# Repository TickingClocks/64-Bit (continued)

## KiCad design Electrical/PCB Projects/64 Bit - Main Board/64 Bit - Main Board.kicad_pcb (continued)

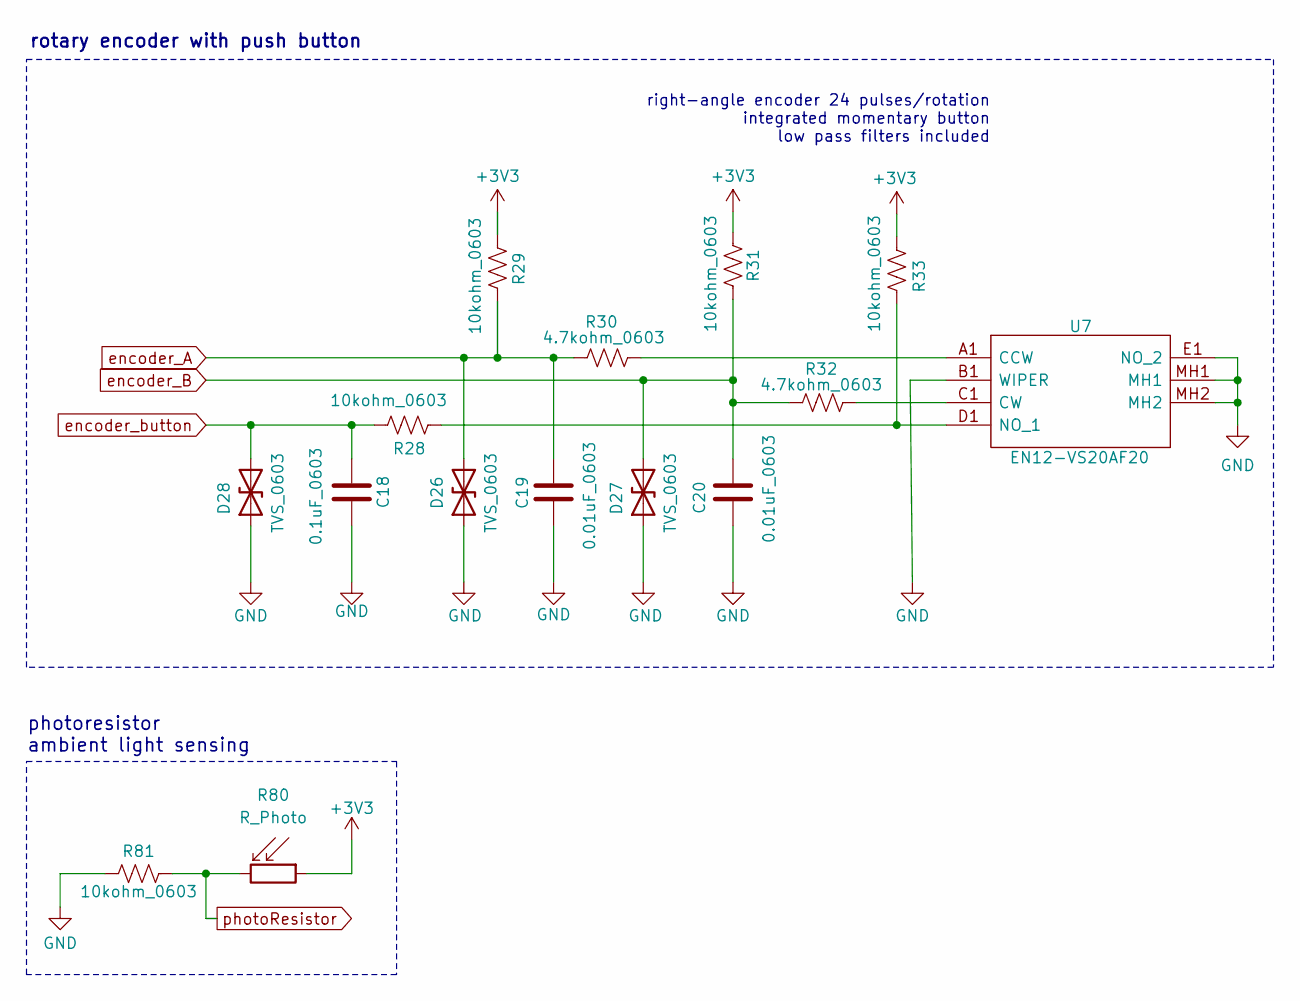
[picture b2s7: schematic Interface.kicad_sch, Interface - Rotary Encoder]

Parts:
C18: 0.1uF_0603; C_0603_1608Metric
C19, C20: 0.01uF_0603; C_0603_1608Metric
D26, D27, D28: TVS_0603; R_0603_1608Metric
R28, R29, R31, R33, R81: 10kohm_0603; R_0603_1608Metric
R30, R32: 4.7kohm_0603; R_0603_1608Metric
R80: R_Photo; R_LDR_5.1x4.3mm_P3.4mm_Vertical
U7: EN12-VS20AF20; Mouser Part Number 858-EN12VS20AF20

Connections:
+3V3: R29.1, R31.1, R33.2, R80.1; also elsewhere on the board
GND: C18.2, C19.1, C20.2, D26.1 (A1), D27.1 (A1), D28.1 (A1), R81.1, U7.B1 (WIPER), U7.E1 (NO_2), U7.MH1, U7.MH2; also elsewhere on the board
unnamed: R30.2, U7.A1 (CCW)
unnamed: R32.2, U7.C1 (CW)
unnamed: R28.1, R33.1, U7.D1 (NO_1)
encoder_A: C19.2, D26.2 (A2), R29.2, R30.1; also elsewhere on the board
encoder_B: C20.1, D27.2 (A2), R31.2, R32.1; also elsewhere on the board
encoder_button: C18.1, D28.2 (A2), R28.2; also elsewhere on the board
photoResistor: R80.2, R81.2; also elsewhere on the board

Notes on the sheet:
right-angle encoder 24 pulses/rotation integrated momentary button low pass filters included
photoresistor ambient light sensing
rotary encoder with push button

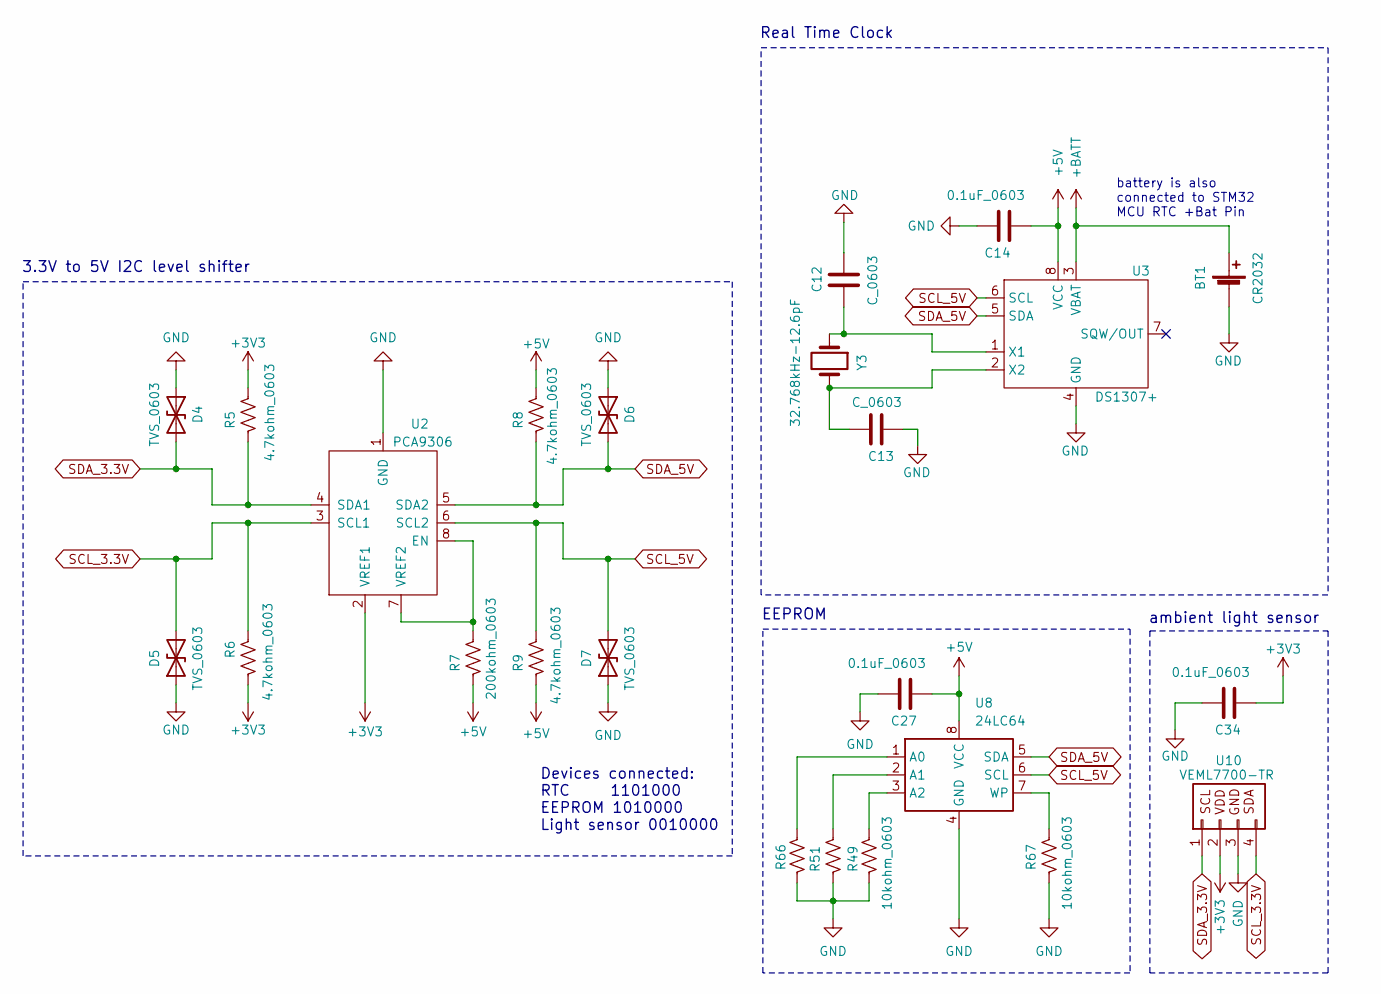
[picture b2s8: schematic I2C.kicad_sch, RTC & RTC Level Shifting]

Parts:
BT1: CR2032; CR2030_HLDR
C12, C13: C_0603; C_0603_1608Metric
C14, C27, C34: 0.1uF_0603; C_0603_1608Metric
D4, D5, D6, D7: TVS_0603; R_0603_1608Metric
R5, R6, R8, R9: 4.7kohm_0603; R_0603_1608Metric
R7: 200kohm_0603; R_0603_1608Metric
R49, R51, R66, R67: 10kohm_0603; R_0603_1608Metric
U2: PCA9306
U3: DS1307+; DS1307
U8: 24LC64; 24LC64F-ISN
U10: VEML7700-TR; VEML7700
Y3: 32.768kHz-12.6pF; 37.768kHz

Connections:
+3V3: C34.2, R5.2, R6.1, U2.2 (VREF1), U10.2 (VDD); also elsewhere on the board
+5V: C14.2, C27.2, R7.1, R8.2, R9.1, U3.8 (VCC), U8.8 (VCC); also elsewhere on the board
+BATT: BT1.1 (+), U3.3 (VBAT); also elsewhere on the board
GND: BT1.2 (-), C12.2, C13.1, C14.1, C27.1, C34.1, D4.1 (A1), D5.1 (A1), D6.1 (A1), D7.1 (A1), R49.1, R51.1, R66.1, R67.1, U2.1 (GND), U3.4 (GND), U8.4 (GND), U10.3 (GND); also elsewhere on the board
unnamed: R7.2, U2.7 (VREF2), U2.8 (EN)
unnamed: C12.1, U3.1 (X1), Y3.1
unnamed: C13.2, U3.2 (X2), Y3.2
unnamed: R66.2, U8.1 (A0)
unnamed: R51.2, U8.2 (A1)
unnamed: R49.2, U8.3 (A2)
unnamed: R67.2, U8.7 (WP)
SCL_3.3V: D5.2 (A2), R6.2, U2.3 (SCL1), U10.4 (SDA); also elsewhere on the board
SCL_5V: D7.2 (A2), R9.2, U2.6 (SCL2), U3.6 (SCL), U8.6 (SCL); also elsewhere on the board
SDA_3.3V: D4.2 (A2), R5.1, U2.4 (SDA1), U10.1 (SCL); also elsewhere on the board
SDA_5V: D6.2 (A2), R8.1, U2.5 (SDA2), U3.5 (SDA), U8.5 (SDA); also elsewhere on the board

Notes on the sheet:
battery is also connected to STM32 MCU RTC +Bat Pin
Devices connected: RTC 1101000 EEPROM 1010000 Light sensor 0010000
Real Time Clock
ambient light sensor
EEPROM
3.3V to 5V I2C level shifter

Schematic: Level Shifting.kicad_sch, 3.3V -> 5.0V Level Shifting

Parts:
C15, C16, C17: 0.1uF_0603; C_0603_1608Metric
D8, D9, D10, D11, D12, D13, D14, D15, D16, D17, D18, D19, D20, D21, D22, D23, D24, D25: TVS_0603; R_0603_1608Metric
R10, R11, R12, R13, R14, R15, R16, R17, R18, R19, R21, R25, R26, R27: 300ohm_0603; R_0603_1608Metric
R20, R22, R23, R24: 22ohm_0603; R_0603_1608Metric
U4, U5, U6: 74HC3G34DC

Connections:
+5V: C15.1, C16.1, C17.1, U4.8 (VCC), U5.8 (VCC), U6.8 (VCC); also elsewhere on the board
GND: C15.2, C16.2, C17.2, D8.1 (A1), D9.1 (A1), D10.1 (A1), D11.1 (A1), D12.1 (A1), D13.1 (A1), D14.1 (A1), D15.1 (A1), D16.1 (A1), D17.1 (A1), D18.1 (A1), D19.1 (A1), D20.1 (A1), D21.1 (A1), D22.1 (A1), D23.1 (A1), D24.1 (A1), D25.1 (A1), U4.4 (GND), U5.4 (GND), U6.4 (GND); also elsewhere on the board
MCU_safetyEnable_1: R15.2; also elsewhere on the board
MCU_safetyEnable_1_5V: R24.1; also elsewhere on the board
MCU_safetyEnable_2: R13.2; also elsewhere on the board
MCU_safetyEnable_2_5V: R22.1; also elsewhere on the board
unnamed: D8.2 (A2), R16.1, U4.1 (1A)
unnamed: D9.2 (A2), R10.1, U5.1 (1A)
unnamed: D10.2 (A2), R13.1, U6.1 (1A)
unnamed: D11.2 (A2), R17.1, U4.3 (2A)
unnamed: D12.2 (A2), R11.1, U5.3 (2A)
unnamed: D13.2 (A2), R14.1, U6.3 (2A)
unnamed: D14.2 (A2), R18.1, U4.6 (3A)
unnamed: D15.2 (A2), R12.2, U5.6 (3A)
unnamed: D16.2 (A2), R15.1, U6.6 (3A)
unnamed: D17.2 (A2), R24.2, U6.2 (3Y)
unnamed: D18.2 (A2), R27.1, U4.2 (3Y)
unnamed: D19.2 (A2), R21.1, U5.2 (3Y)
unnamed: D20.2 (A2), R23.2, U6.5 (2Y)
unnamed: D21.2 (A2), R26.2, U4.5 (2Y)
unnamed: D22.2 (A2), R20.2, U5.5 (2Y)
unnamed: D23.2 (A2), R22.2, U6.7 (1Y)
unnamed: D24.2 (A2), R25.2, U4.7 (1Y)
unnamed: D25.2 (A2), R19.2, U5.7 (1Y)
hv_output_relay: R23.1; also elsewhere on the board
mcu_hv_output_relay: R14.2; also elsewhere on the board
mcu_neopixel: R11.2; also elsewhere on the board
mcu_nixie_RCLK: R12.1; also elsewhere on the board
mcu_nixie_SRCK: R16.2; also elsewhere on the board
mcu_nixie_SRCLK: R17.2; also elsewhere on the board
mcu_nixie_data: R18.2; also elsewhere on the board
mcu_nixie_display_enable: R10.2; also elsewhere on the board
neopixel: R20.1; also elsewhere on the board
nixie_RCLK: R21.2; also elsewhere on the board
nixie_SRCK: R25.1; also elsewhere on the board
nixie_SRCLK: R26.1; also elsewhere on the board
nixie_data: R27.2; also elsewhere on the board
nixie_display_enable: R19.1; also elsewhere on the board

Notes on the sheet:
safetyEnable Signals from MCU
shift register signals from MCU
shift register signals to display PCB
neopixel to display PCB
neopixel from MCU
safetyEnable Signals to transistors

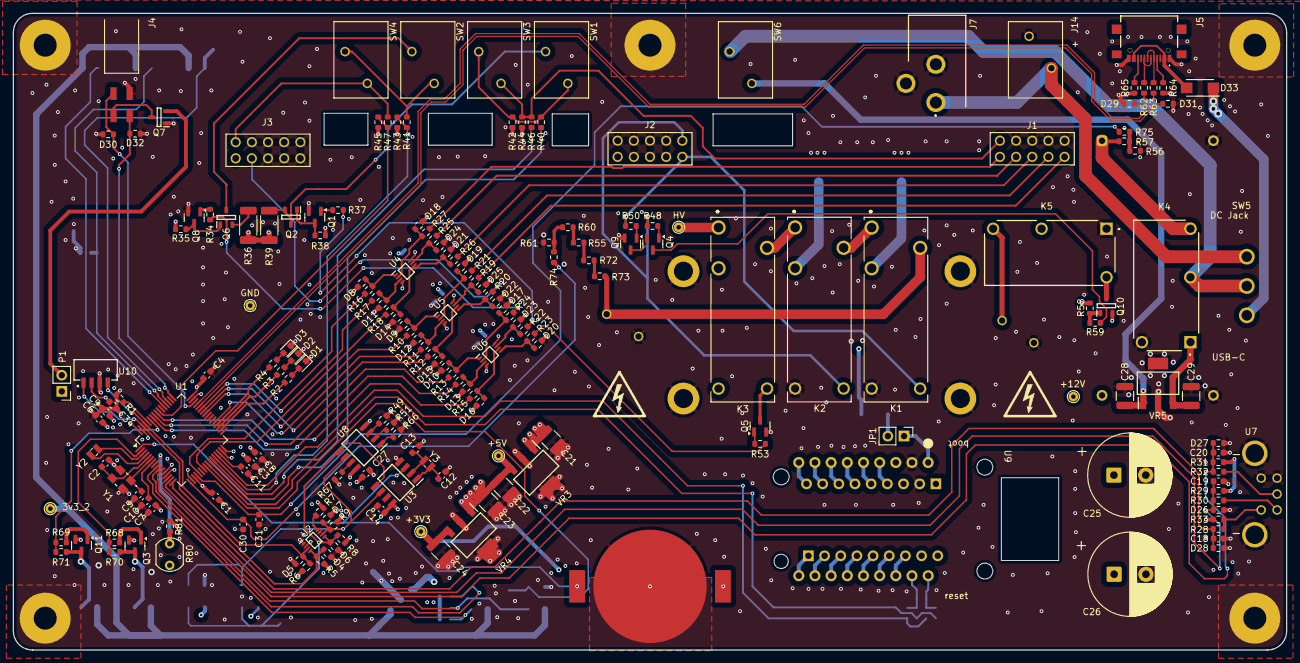
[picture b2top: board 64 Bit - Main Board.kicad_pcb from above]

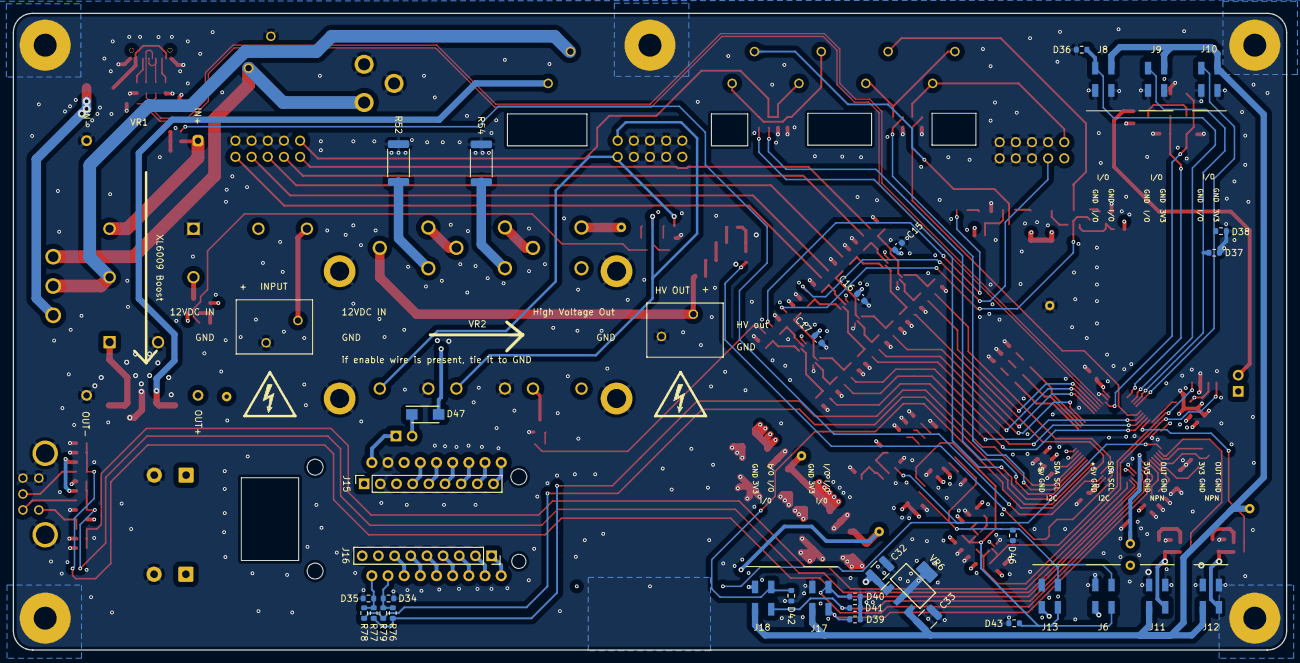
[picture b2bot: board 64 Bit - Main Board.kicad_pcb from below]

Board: 4 copper layers, 200.0 x 100.0 mm, 233 parts (37 on the bottom side), 162 nets.

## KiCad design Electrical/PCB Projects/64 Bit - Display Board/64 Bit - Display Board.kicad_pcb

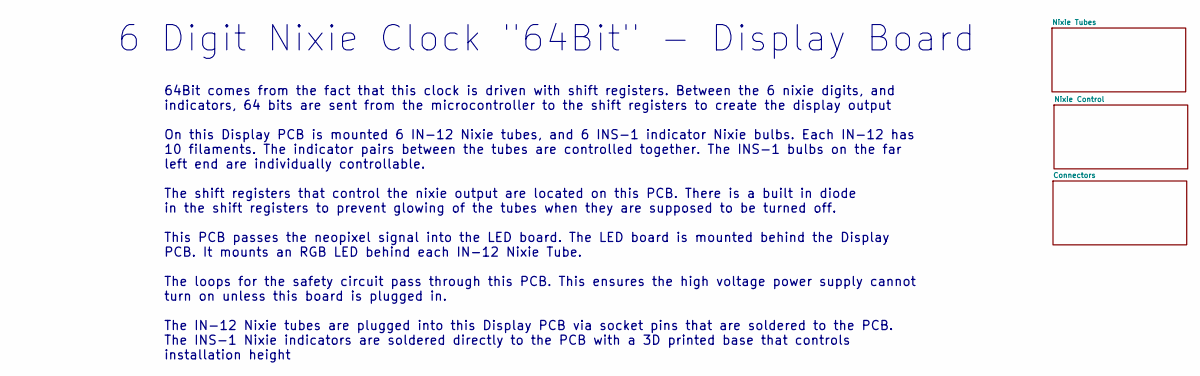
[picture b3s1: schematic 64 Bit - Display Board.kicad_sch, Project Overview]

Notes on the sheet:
6 Digit Nixie Clock "64Bit" - Display Board
64Bit comes from the fact that this clock is driven with shift registers. Between the 6 nixie digits, and indicators, 64 bits are sent from the microcontroller to the shift registers to create the display output On this Display PCB is mounted 6 IN-12 Nixie tubes, and 6 INS-1 indicator Nixie bulbs. 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

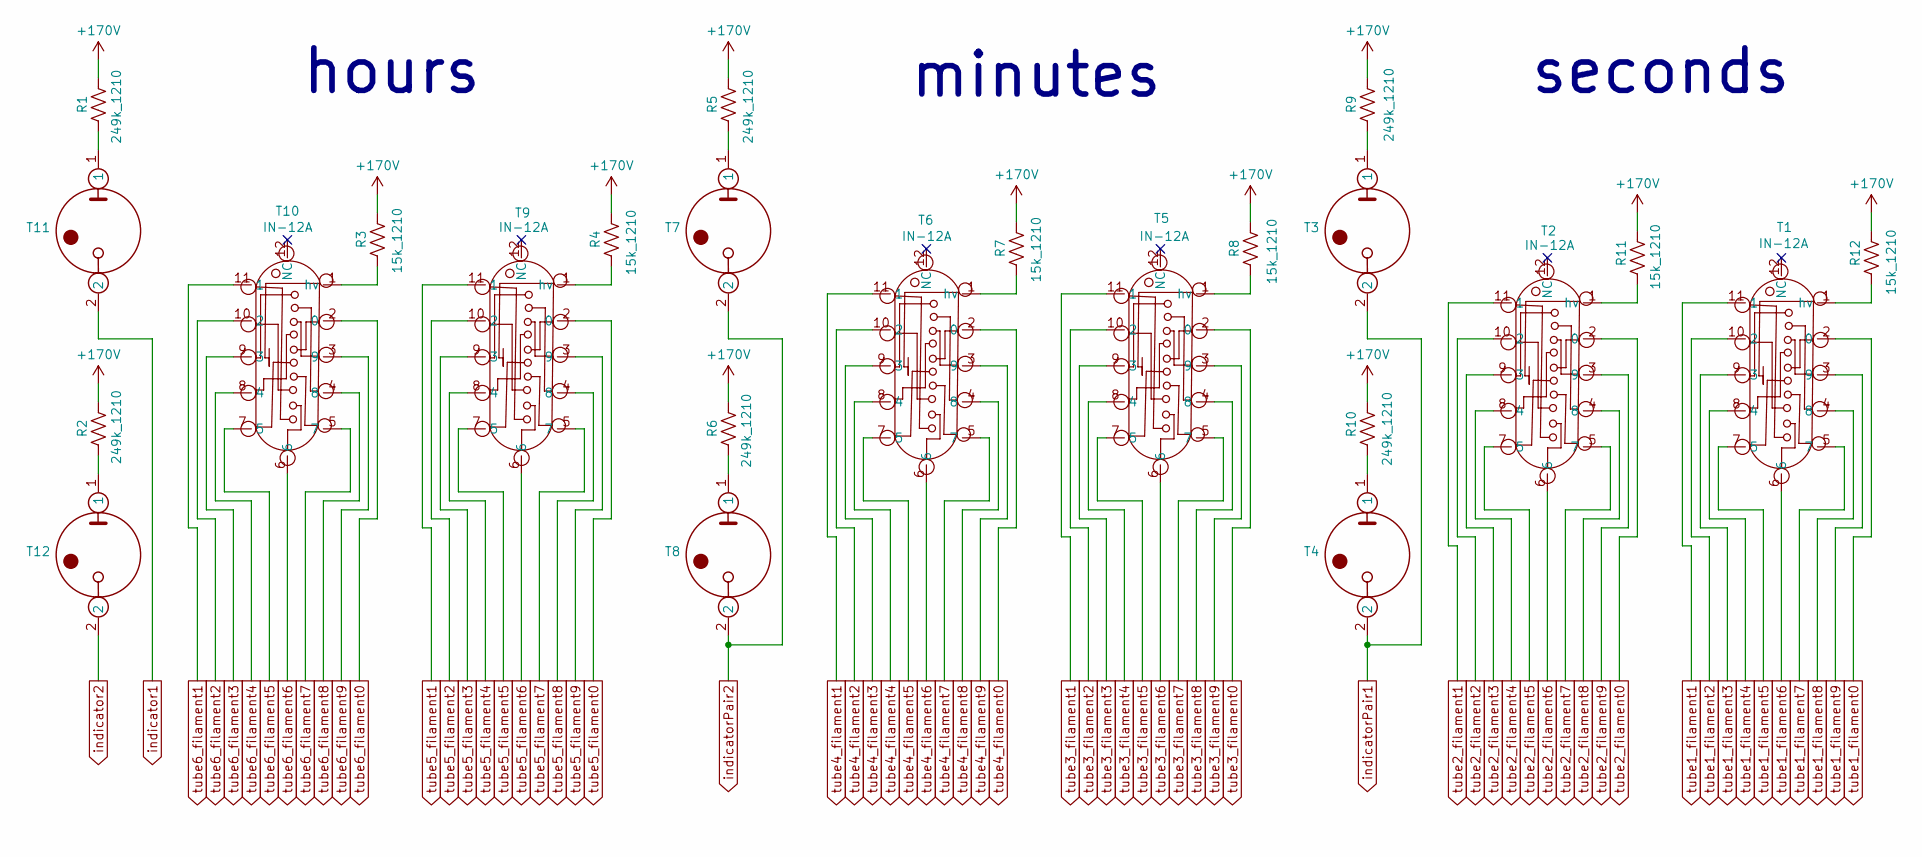
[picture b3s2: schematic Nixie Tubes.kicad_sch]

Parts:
R1, R2, R5, R6, R9, R10: 249k_1210; C_1210_3225Metric
R3, R4, R7, R8, R11, R12: 15k_1210; C_1210_3225Metric
T1, T2, T5, T6, T9, T10: IN-12A; IN-12
T3, T4, T7, T8, T11, T12: INS-1

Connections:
+170V: R1.1, R2.1, R3.1, R4.1, R5.1, R6.1, R7.1, R8.1, R9.1, R10.1, R11.1, R12.1; also elsewhere on the board
unnamed: R1.2, T11.1
unnamed: R2.2, T12.1
unnamed: R5.2, T7.1
unnamed: R6.2, T8.1
unnamed: R9.2, T3.1
unnamed: R10.2, T4.1
unnamed: R12.2, T1.1 (hv)
unnamed: R11.2, T2.1 (hv)
unnamed: R8.2, T5.1 (hv)
unnamed: R7.2, T6.1 (hv)
unnamed: R4.2, T9.1 (hv)
unnamed: R3.2, T10.1 (hv)
indicator1: T11.2; also elsewhere on the board
indicator2: T12.2; also elsewhere on the board
indicatorPair1: T3.2, T4.2; also elsewhere on the board
indicatorPair2: T7.2, T8.2; also elsewhere on the board
tube1_filament0: T1.2 (0); also elsewhere on the board
tube1_filament1: T1.11 (1); also elsewhere on the board
tube1_filament2: T1.10 (2); also elsewhere on the board
tube1_filament3: T1.9 (3); also elsewhere on the board
tube1_filament4: T1.8 (4); also elsewhere on the board
tube1_filament5: T1.7 (5); also elsewhere on the board
tube1_filament6: T1.6; also elsewhere on the board
tube1_filament7: T1.5 (7); also elsewhere on the board
tube1_filament8: T1.4 (8); also elsewhere on the board
tube1_filament9: T1.3 (9); also elsewhere on the board
tube2_filament0: T2.2 (0); also elsewhere on the board
tube2_filament1: T2.11 (1); also elsewhere on the board
tube2_filament2: T2.10 (2); also elsewhere on the board
tube2_filament3: T2.9 (3); also elsewhere on the board
tube2_filament4: T2.8 (4); also elsewhere on the board
tube2_filament5: T2.7 (5); also elsewhere on the board
tube2_filament6: T2.6; also elsewhere on the board
tube2_filament7: T2.5 (7); also elsewhere on the board
tube2_filament8: T2.4 (8); also elsewhere on the board
tube2_filament9: T2.3 (9); also elsewhere on the board
tube3_filament0: T5.2 (0); also elsewhere on the board
tube3_filament1: T5.11 (1); also elsewhere on the board
tube3_filament2: T5.10 (2); also elsewhere on the board
tube3_filament3: T5.9 (3); also elsewhere on the board
tube3_filament4: T5.8 (4); also elsewhere on the board
tube3_filament5: T5.7 (5); also elsewhere on the board
tube3_filament6: T5.6; also elsewhere on the board
tube3_filament7: T5.5 (7); also elsewhere on the board
tube3_filament8: T5.4 (8); also elsewhere on the board
tube3_filament9: T5.3 (9); also elsewhere on the board
tube4_filament0: T6.2 (0); also elsewhere on the board
tube4_filament1: T6.11 (1); also elsewhere on the board
tube4_filament2: T6.10 (2); also elsewhere on the board
tube4_filament3: T6.9 (3); also elsewhere on the board
tube4_filament4: T6.8 (4); also elsewhere on the board
tube4_filament5: T6.7 (5); also elsewhere on the board
tube4_filament6: T6.6; also elsewhere on the board
tube4_filament7: T6.5 (7); also elsewhere on the board
tube4_filament8: T6.4 (8); also elsewhere on the board
tube4_filament9: T6.3 (9); also elsewhere on the board
tube5_filament0: T9.2 (0); also elsewhere on the board
tube5_filament1: T9.11 (1); also elsewhere on the board
tube5_filament2: T9.10 (2); also elsewhere on the board
tube5_filament3: T9.9 (3); also elsewhere on the board
tube5_filament4: T9.8 (4); also elsewhere on the board
tube5_filament5: T9.7 (5); also elsewhere on the board
tube5_filament6: T9.6; also elsewhere on the board
tube5_filament7: T9.5 (7); also elsewhere on the board
tube5_filament8: T9.4 (8); also elsewhere on the board
tube5_filament9: T9.3 (9); also elsewhere on the board
tube6_filament0: T10.2 (0); also elsewhere on the board
tube6_filament1: T10.11 (1); also elsewhere on the board
tube6_filament2: T10.10 (2); also elsewhere on the board
tube6_filament3: T10.9 (3); also elsewhere on the board
tube6_filament4: T10.8 (4); also elsewhere on the board
tube6_filament5: T10.7 (5); also elsewhere on the board
tube6_filament6: T10.6; also elsewhere on the board
tube6_filament7: T10.5 (7); also elsewhere on the board
tube6_filament8: T10.4 (8); also elsewhere on the board
tube6_filament9: T10.3 (9); also elsewhere on the board

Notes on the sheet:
minutes
seconds
hours

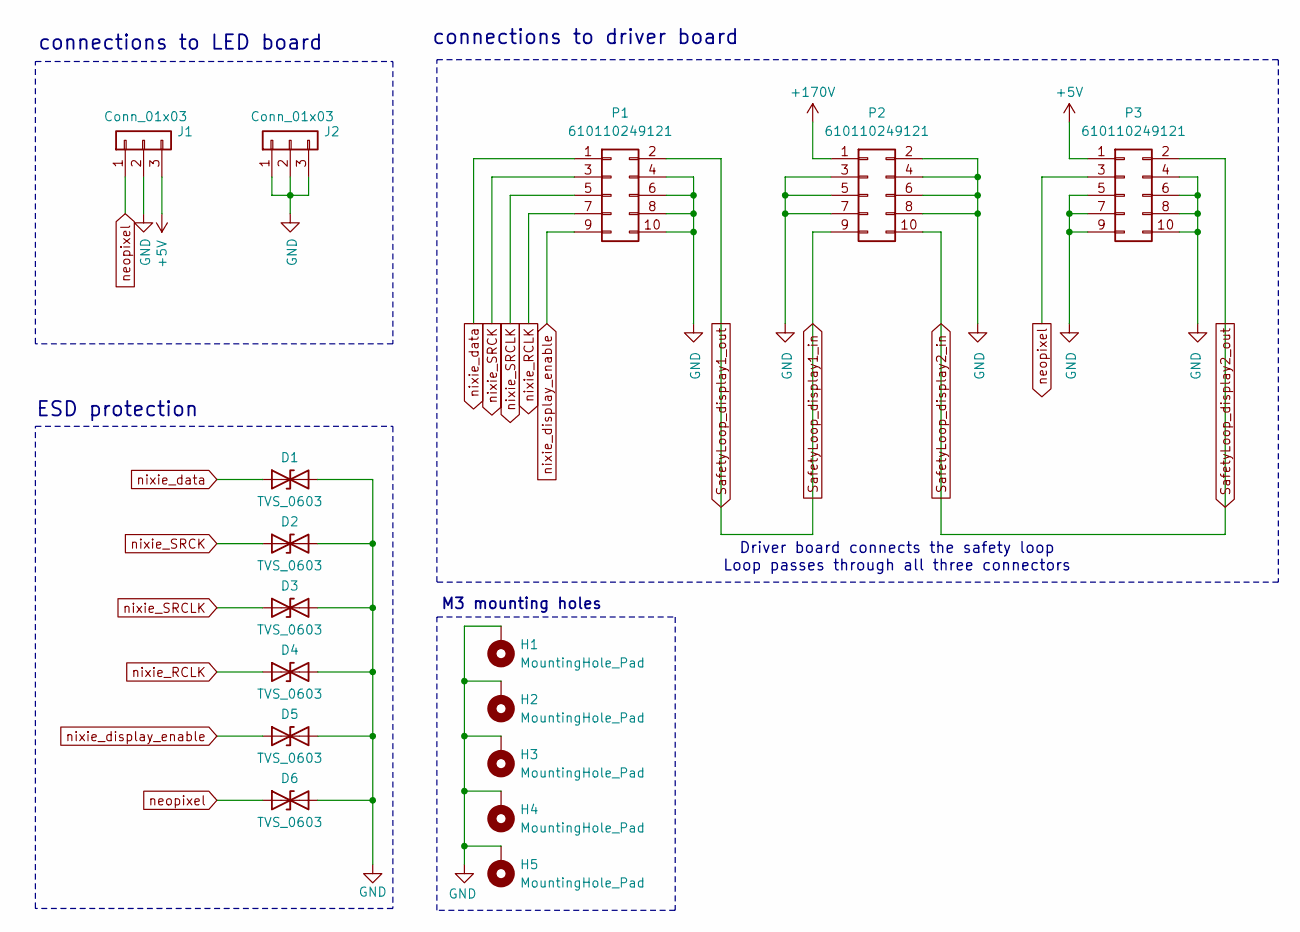
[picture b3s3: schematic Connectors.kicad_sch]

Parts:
D1, D2, D3, D4, D5, D6: TVS_0603; R_0603_1608Metric
H1, H2, H3, H4, H5: MountingHole_Pad; M3 Standoff Footprint
J1, J2: Conn_01x03; PinSocket_1x03_P2.54mm_Vertical
P1, P2, P3: 610110249121

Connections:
+5V: J1.3, P3.1; also elsewhere on the board
+170V: P2.1; also elsewhere on the board
GND: D1.2 (A2), D2.2 (A2), D3.2 (A2), D4.2 (A2), D5.2 (A2), D6.2 (A2), H1.1, H2.1, H3.1, H4.1, H5.1, J1.2, J2.1, J2.2, J2.3, P1.4, P1.6, P1.8, P1.10, P2.2, P2.3, P2.4, P2.5, P2.6, P2.7, P2.8, P3.4, P3.5, P3.6, P3.7, P3.8, P3.9, P3.10; also elsewhere on the board
SafetyLoop_display1_in: P1.2, P2.9
SafetyLoop_display2_in: P2.10, P3.2
neopixel: D6.1 (A1), J1.1, P3.3
nixie_RCLK: D4.1 (A1), P1.7; also elsewhere on the board
nixie_SRCK: D2.1 (A1), P1.3; also elsewhere on the board
nixie_SRCLK: D3.1 (A1), P1.5; also elsewhere on the board
nixie_data: D1.1 (A1), P1.1; also elsewhere on the board
nixie_display_enable: D5.1 (A1), P1.9; also elsewhere on the board

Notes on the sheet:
Driver board connects the safety loop Loop passes through all three connectors
connections to driver board
connections to LED board
ESD protection
M3 mounting holes

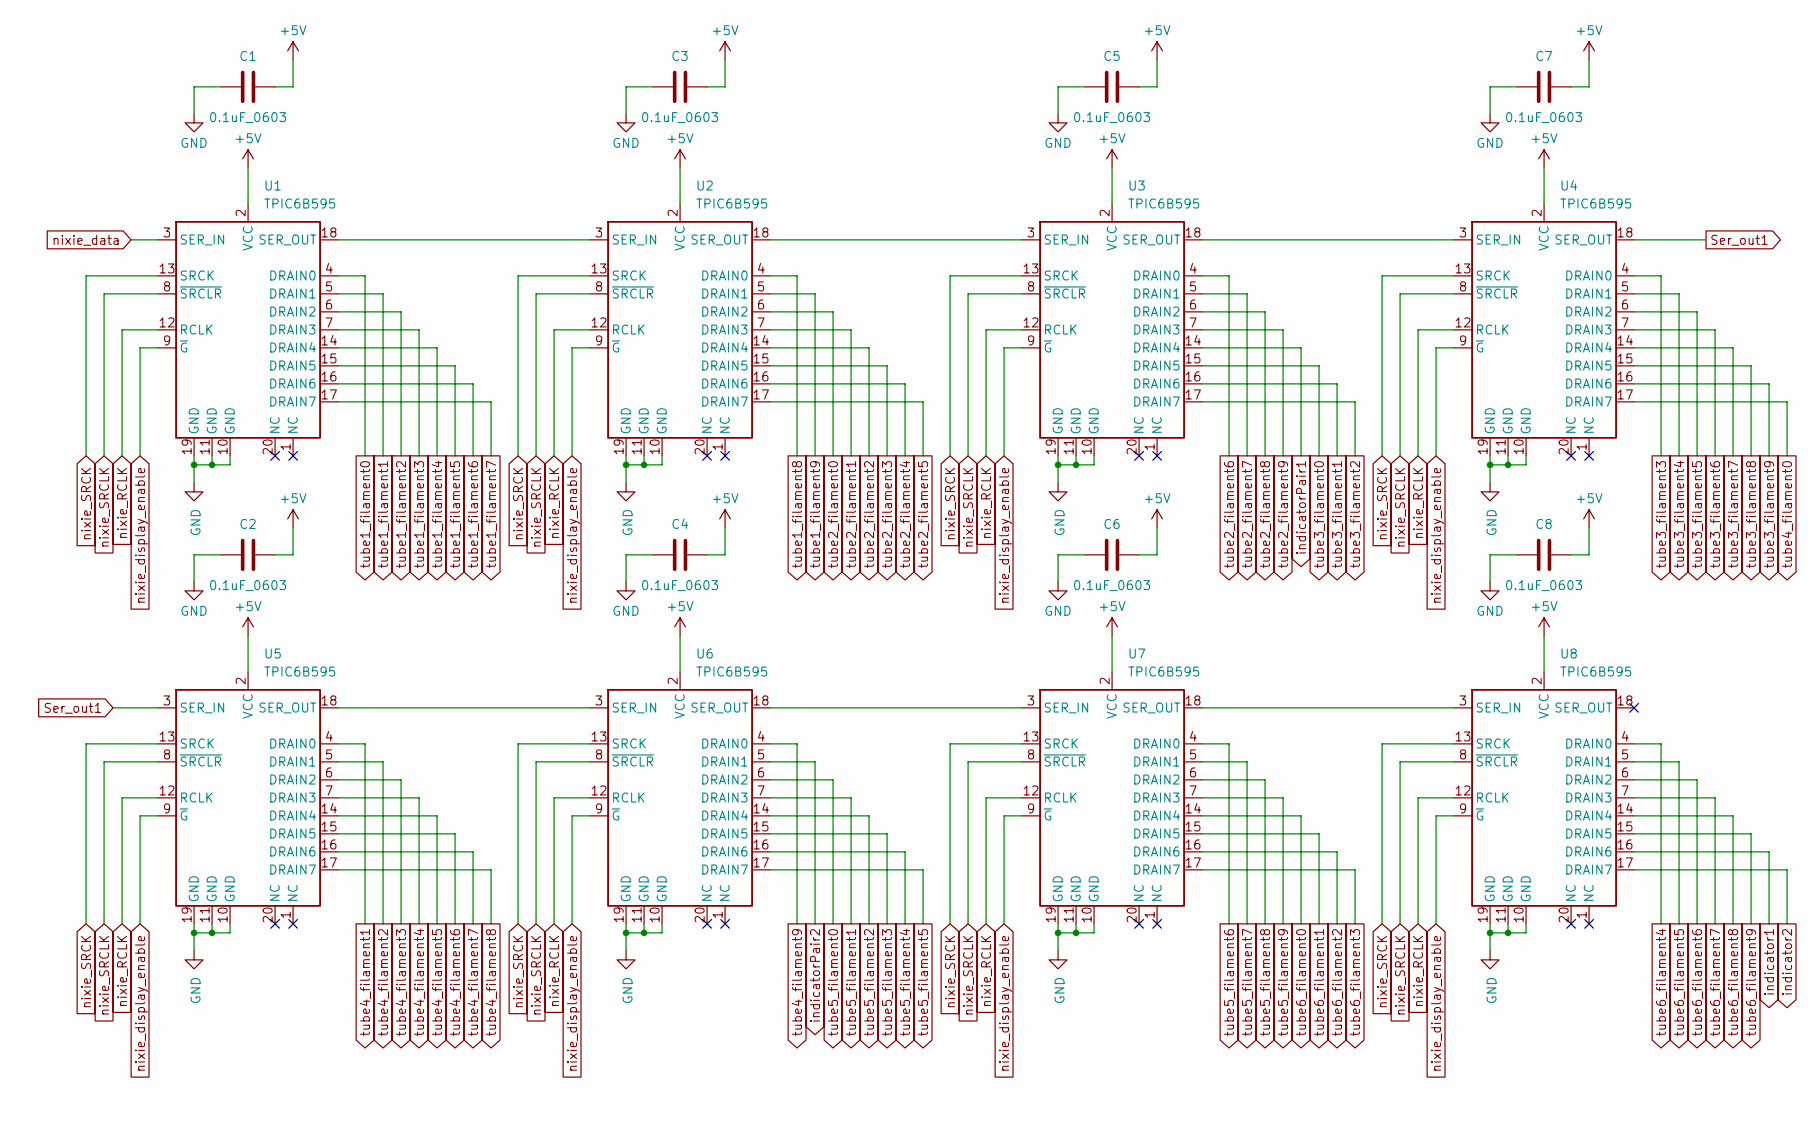
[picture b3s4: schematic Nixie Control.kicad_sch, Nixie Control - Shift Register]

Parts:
C1, C2, C3, C4, C5, C6, C7, C8: 0.1uF_0603; C_0603_1608Metric
U1, U2, U3, U4, U5, U6, U7, U8: TPIC6B595; TPIC6B595DWR

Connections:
+5V: C1.2, C2.2, C3.2, C4.2, C5.2, C6.2, C7.2, C8.2, U1.2 (VCC), U2.2 (VCC), U3.2 (VCC), U4.2 (VCC), U5.2 (VCC), U6.2 (VCC), U7.2 (VCC), U8.2 (VCC); also elsewhere on the board
GND: C1.1, C2.1, C3.1, C4.1, C5.1, C6.1, C7.1, C8.1, U1.10 (GND), U1.11 (GND), U1.19 (GND), U2.10 (GND), U2.11 (GND), U2.19 (GND), U3.10 (GND), U3.11 (GND), U3.19 (GND), U4.10 (GND), U4.11 (GND), U4.19 (GND), U5.10 (GND), U5.11 (GND), U5.19 (GND), U6.10 (GND), U6.11 (GND), U6.19 (GND), U7.10 (GND), U7.11 (GND), U7.19 (GND), U8.10 (GND), U8.11 (GND), U8.19 (GND); also elsewhere on the board
unnamed: U1.18 (SER_OUT), U2.3 (SER_IN)
unnamed: U2.18 (SER_OUT), U3.3 (SER_IN)
unnamed: U3.18 (SER_OUT), U4.3 (SER_IN)
unnamed: U5.18 (SER_OUT), U6.3 (SER_IN)
unnamed: U6.18 (SER_OUT), U7.3 (SER_IN)
unnamed: U7.18 (SER_OUT), U8.3 (SER_IN)
Ser_out1: U4.18 (SER_OUT), U5.3 (SER_IN)
indicator1: U8.16 (DRAIN6); also elsewhere on the board
indicator2: U8.17 (DRAIN7); also elsewhere on the board
indicatorPair1: U3.14 (DRAIN4); also elsewhere on the board
indicatorPair2: U6.5 (DRAIN1); also elsewhere on the board
nixie_RCLK: U1.12 (RCLK), U2.12 (RCLK), U3.12 (RCLK), U4.12 (RCLK), U5.12 (RCLK), U6.12 (RCLK), U7.12 (RCLK), U8.12 (RCLK); also elsewhere on the board
nixie_SRCK: U1.13 (SRCK), U2.13 (SRCK), U3.13 (SRCK), U4.13 (SRCK), U5.13 (SRCK), U6.13 (SRCK), U7.13 (SRCK), U8.13 (SRCK); also elsewhere on the board
nixie_SRCLK: U1.8 (~SRCLR), U2.8 (~SRCLR), U3.8 (~SRCLR), U4.8 (~SRCLR), U5.8 (~SRCLR), U6.8 (~SRCLR), U7.8 (~SRCLR), U8.8 (~SRCLR); also elsewhere on the board
nixie_data: U1.3 (SER_IN); also elsewhere on the board
nixie_display_enable: U1.9 (~G), U2.9 (~G), U3.9 (~G), U4.9 (~G), U5.9 (~G), U6.9 (~G), U7.9 (~G), U8.9 (~G); also elsewhere on the board
tube1_filament0: U1.4 (DRAIN0); also elsewhere on the board
tube1_filament1: U1.5 (DRAIN1); also elsewhere on the board
tube1_filament2: U1.6 (DRAIN2); also elsewhere on the board
tube1_filament3: U1.7 (DRAIN3); also elsewhere on the board
tube1_filament4: U1.14 (DRAIN4); also elsewhere on the board
tube1_filament5: U1.15 (DRAIN5); also elsewhere on the board
tube1_filament6: U1.16 (DRAIN6); also elsewhere on the board
tube1_filament7: U1.17 (DRAIN7); also elsewhere on the board
tube1_filament8: U2.4 (DRAIN0); also elsewhere on the board
tube1_filament9: U2.5 (DRAIN1); also elsewhere on the board
tube2_filament0: U2.6 (DRAIN2); also elsewhere on the board
tube2_filament1: U2.7 (DRAIN3); also elsewhere on the board
tube2_filament2: U2.14 (DRAIN4); also elsewhere on the board
tube2_filament3: U2.15 (DRAIN5); also elsewhere on the board
tube2_filament4: U2.16 (DRAIN6); also elsewhere on the board
tube2_filament5: U2.17 (DRAIN7); also elsewhere on the board
tube2_filament6: U3.4 (DRAIN0); also elsewhere on the board
tube2_filament7: U3.5 (DRAIN1); also elsewhere on the board
tube2_filament8: U3.6 (DRAIN2); also elsewhere on the board
tube2_filament9: U3.7 (DRAIN3); also elsewhere on the board
tube3_filament0: U3.15 (DRAIN5); also elsewhere on the board
tube3_filament1: U3.16 (DRAIN6); also elsewhere on the board
tube3_filament2: U3.17 (DRAIN7); also elsewhere on the board
tube3_filament3: U4.4 (DRAIN0); also elsewhere on the board
tube3_filament4: U4.5 (DRAIN1); also elsewhere on the board
tube3_filament5: U4.6 (DRAIN2); also elsewhere on the board
tube3_filament6: U4.7 (DRAIN3); also elsewhere on the board
tube3_filament7: U4.14 (DRAIN4); also elsewhere on the board
tube3_filament8: U4.15 (DRAIN5); also elsewhere on the board
tube3_filament9: U4.16 (DRAIN6); also elsewhere on the board
tube4_filament0: U4.17 (DRAIN7); also elsewhere on the board
tube4_filament1: U5.4 (DRAIN0); also elsewhere on the board
tube4_filament2: U5.5 (DRAIN1); also elsewhere on the board
tube4_filament3: U5.6 (DRAIN2); also elsewhere on the board
tube4_filament4: U5.7 (DRAIN3); also elsewhere on the board
tube4_filament5: U5.14 (DRAIN4); also elsewhere on the board
tube4_filament6: U5.15 (DRAIN5); also elsewhere on the board
tube4_filament7: U5.16 (DRAIN6); also elsewhere on the board
tube4_filament8: U5.17 (DRAIN7); also elsewhere on the board
tube4_filament9: U6.4 (DRAIN0); also elsewhere on the board
tube5_filament0: U6.6 (DRAIN2); also elsewhere on the board
tube5_filament1: U6.7 (DRAIN3); also elsewhere on the board
tube5_filament2: U6.14 (DRAIN4); also elsewhere on the board
tube5_filament3: U6.15 (DRAIN5); also elsewhere on the board
tube5_filament4: U6.16 (DRAIN6); also elsewhere on the board
tube5_filament5: U6.17 (DRAIN7); also elsewhere on the board
tube5_filament6: U7.4 (DRAIN0); also elsewhere on the board
tube5_filament7: U7.5 (DRAIN1); also elsewhere on the board
tube5_filament8: U7.6 (DRAIN2); also elsewhere on the board
tube5_filament9: U7.7 (DRAIN3); also elsewhere on the board
tube6_filament0: U7.14 (DRAIN4); also elsewhere on the board
tube6_filament1: U7.15 (DRAIN5); also elsewhere on the board
tube6_filament2: U7.16 (DRAIN6); also elsewhere on the board
tube6_filament3: U7.17 (DRAIN7); also elsewhere on the board
tube6_filament4: U8.4 (DRAIN0); also elsewhere on the board
tube6_filament5: U8.5 (DRAIN1); also elsewhere on the board
tube6_filament6: U8.6 (DRAIN2); also elsewhere on the board
tube6_filament7: U8.7 (DRAIN3); also elsewhere on the board
tube6_filament8: U8.14 (DRAIN4); also elsewhere on the board
tube6_filament9: U8.15 (DRAIN5); also elsewhere on the board

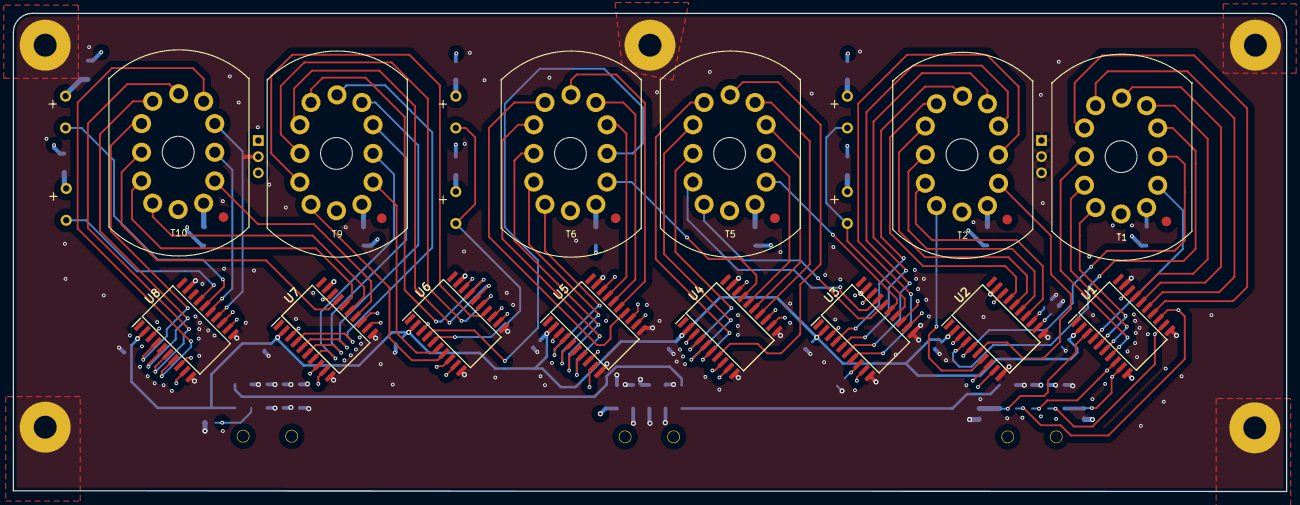
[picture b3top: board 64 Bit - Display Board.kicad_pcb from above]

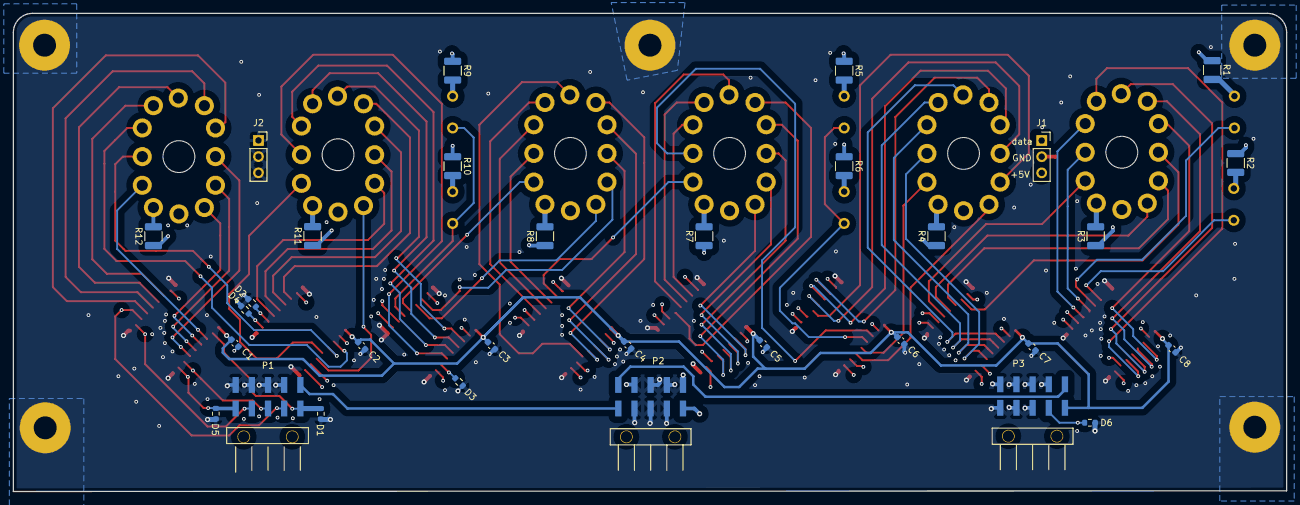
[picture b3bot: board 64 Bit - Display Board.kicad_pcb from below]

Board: 4 copper layers, 200.0 x 75.1 mm, 56 parts (31 on the bottom side), 94 nets.

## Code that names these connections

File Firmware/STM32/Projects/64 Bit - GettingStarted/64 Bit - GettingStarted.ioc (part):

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Mcu.Name=STM32F446R(C-E)Tx
Mcu.Package=LQFP64
Mcu.UserName=STM32F446RETx
PA0-WKUP.Signal=S_TIM2_CH1_ETR
PA1.Signal=S_TIM2_CH2
PA10.GPIOParameters=GPIO_Label
PA10.GPIO_Label=nixie_SRCLK
PA10.Signal=GPIO_Output
PA11.Mode=Device_Only
PA11.Signal=USB_OTG_FS_DM
PA12.Mode=Device_Only
PA12.Signal=USB_OTG_FS_DP
PA13.Mode=Serial_Wire
PA13.Signal=SYS_JTMS-SWDIO
PA14.Mode=Serial_Wire
PA14.Signal=SYS_JTCK-SWCLK
PA2.GPIOParameters=GPIO_Label
PA2.GPIO_Label=button_encoder
PA2.Signal=GPIO_Output
PA3.Signal=ADCx_IN3
PA4.Signal=ADCx_IN4
PA5.Mode=TX_Only_Simplex_Unidirect_Master
PA5.Signal=SPI1_SCK
PA7.Mode=TX_Only_Simplex_Unidirect_Master
PA7.Signal=SPI1_MOSI
PA8.GPIOParameters=GPIO_Label
PA8.GPIO_Label=nixie_display_enable
PA8.Signal=GPIO_Output
PA9.GPIOParameters=GPIO_Label
PA9.GPIO_Label=nixie_RCLK
PA9.Signal=GPIO_Output
PB0.GPIOParameters=GPIO_Label
PB0.GPIO_Label=safetyStatus1
PB0.Signal=GPIO_Input
PB1.GPIOParameters=GPIO_Label
PB1.GPIO_Label=safetyStatus2
PB1.Signal=GPIO_Input
PB10.Mode=Asynchronous
PB10.Signal=USART3_TX
PB13.GPIOParameters=GPIO_Label
PB13.GPIO_Label=led1
PB13.Signal=GPIO_Output
PB14.GPIOParameters=GPIO_Label
PB14.GPIO_Label=led2
PB14.Signal=GPIO_Output
PB15.GPIOParameters=GPIO_Label
PB15.GPIO_Label=led3
PB15.Signal=GPIO_Output
PB2.GPIOParameters=GPIO_Label
PB2.GPIO_Label=safetyStatus3
PB2.Signal=GPIO_Input
PB3.GPIOParameters=GPIO_Label
PB3.GPIO_Label=safetyStatus4
PB3.Signal=GPIO_Input
PB4.GPIOParameters=GPIO_Label
PB4.GPIO_Label=safetyEnable1
PB4.Signal=GPIO_Output
PB5.GPIOParameters=GPIO_Label
PB5.GPIO_Label=safetyEnable2
PB5.Signal=GPIO_Output
PB6.GPIOParameters=GPIO_Label
PB6.GPIO_Label=hvOutputRelay
PB6.Signal=GPIO_Output
PB7.GPIOParameters=GPIO_Label
PB7.GPIO_Label=IO5
PB7.Signal=GPIO_Output
PB8.Mode=I2C
PB8.Signal=I2C1_SCL
PB9.Mode=I2C
PB9.Signal=I2C1_SDA
PC0.Signal=ADCx_IN10
PC1.GPIOParameters=GPIO_Label
PC1.GPIO_Label=IO6
PC1.Signal=GPIO_Input
PC10.GPIOParameters=GPIO_Label
PC10.GPIO_Label=IO1
PC10.Signal=GPIO_Output
PC11.GPIOParameters=GPIO_Label
PC11.GPIO_Label=IO2
PC11.Signal=GPIO_Output
PC12.GPIOParameters=GPIO_Label
PC12.GPIO_Label=IO3
PC12.Signal=GPIO_Output
PC13.GPIOParameters=GPIO_Label
PC13.GPIO_Label=IO4
PC13.Signal=GPIO_Output
PC14-OSC32_IN.Mode=LSE-External-Oscillator
PC14-OSC32_IN.Signal=RCC_OSC32_IN
PC15-OSC32_OUT.Mode=LSE-External-Oscillator
PC15-OSC32_OUT.Signal=RCC_OSC32_OUT
PC2.GPIOParameters=GPIO_Label
PC2.GPIO_Label=IO7
PC2.Signal=GPIO_Input
PC3.GPIOParameters=GPIO_Label
PC3.GPIO_Label=IO8
PC3.Signal=GPIO_Input
PC5.Mode=Asynchronous
PC5.Signal=USART3_RX
PC6.GPIOParameters=GPIO_Label
PC6.GPIO_Label=neopixel
PC6.Signal=S_TIM3_CH1
PH0-OSC_IN.Mode=HSE-External-Oscillator
PH0-OSC_IN.Signal=RCC_OSC_IN
PH1-OSC_OUT.Mode=HSE-External-Oscillator
PH1-OSC_OUT.Signal=RCC_OSC_OUT
RCC.HSE_VALUE=16000000
RCC.SYSCLKFreq_VALUE=168000000
RCC.SYSCLKSource=RCC_SYSCLKSOURCE_PLLRCLK
board=custom

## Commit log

2025-11-21 simple text update in sch proj, git test
2025-11-21 output a new pdf schematic for the mainboard (practicing git)
2025-11-21 fixed folder layout for STM32 projects. Workspace folder should not be in the git directory
2025-11-21 added blinky to stm32 project
2025-11-22 finalized schematic, made ESP32 footprint, started PCB update
2025-11-22 save for night
2025-11-22 ran 3D model consolidate plugin
2025-11-23 small pcb layout work
2025-11-24 finished routing - added photoresistor to analog pin. Updated STM32Cube setup. Final stages of hardware design
2025-11-25 update main description text on front page of schematic
2025-11-28 added I2C ambient light sensor
2025-12-02 near final state. Includes BOM, price, etc
2025-12-05 slight change to copper pours.
2025-12-06 slight changes
2025-12-07 final. PCB outputs generated, ordering prototypes
2025-12-15 added standoffs, updates to 3D exports. starting prototyping/verification 3D printed stand next
2025-12-15 footprints managment
2025-12-22 adding comments after build. Documentation for next revision
2025-12-25 mistake found in the safety circuit. The AND gate is mis-designed for mosfets. Two Pchannel mosfets need to be added and the output signal then inverted. These were added via wires to the hardware an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
